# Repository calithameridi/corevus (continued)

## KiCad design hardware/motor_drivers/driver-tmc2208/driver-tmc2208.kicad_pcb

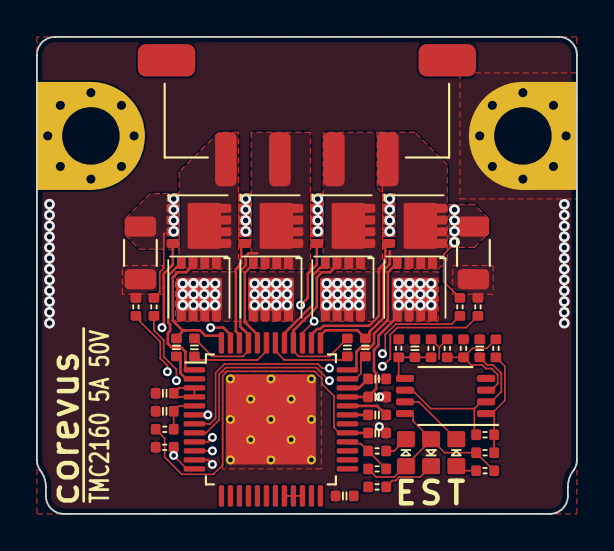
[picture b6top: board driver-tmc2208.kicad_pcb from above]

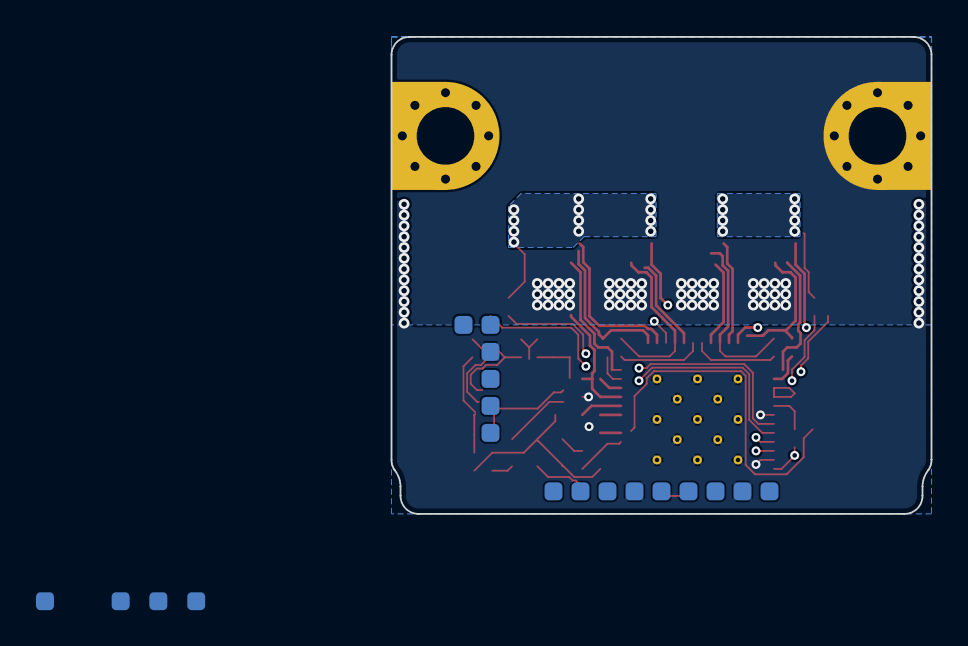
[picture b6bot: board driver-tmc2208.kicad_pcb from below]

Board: 4 copper layers, 30.0 x 26.5 mm, 67 parts (19 on the bottom side), 49 nets.

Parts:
C1: 100nF 16V; 0402C
C2: 22nF 100V; 0402C
C3, C5: 1µF; 0402C
C4, C6, C8, C9, C10, C11: 1μF; 0402C
C7: 100nF 100V; 0402C
C12: 4.7nF; 0402C
C13: 10nF; 0402C
D1: G; 0603LED
D2: Y; 0603LED
D3: R; 0603LED
H1: VM; MountingHole_M3_Driver
H2: Gnd; MountingHole_M3_Driver
M1: Micro-Fit 3.0; XKB_X3025WRS-04D
Q1, Q2, Q3, Q4, Q5, Q6, Q7, Q8: 30N06; MOSFET_DFN8
R1, R16: 1kΩ; 0402R
R2, R3: 10kΩ; 0402R
R4: 2.2Ω; 0402R
R5: AkΩ; 0402R
R6: BkΩ; 0402R
R7: CkΩ; 0402R
R8, R9, R11, R12: 47Ω; 0402R
R10, R13: 30mΩ; R_1206_3216Metric
R14: DkΩ; 0402R
R15: EkΩ; 0402R
R17: 200Ω; 0402R
R20: 4.7kΩ; 0402R
T1, T5, T12: GND; LGA_Land
T2: CLK; LGA_Land
T3: 12V; LGA_Land
T4: SCK; LGA_Land
T6: SDI; LGA_Land
T7: SDO; LGA_Land
T8: VCC; LGA_Land
T9: Therm; LGA_Land
T10: CS0; LGA_Land
T11: STEP; LGA_Land
T13: DIR; LGA_Land
T14: EN; LGA_Land
T17: DIAG0; LGA_Land
T18: DIAG1; LGA_Land
T19: ENCA; LGA_Land
T20: ENCB; LGA_Land
T21: ENCN; LGA_Land
TH1: 10kΩ 3950K; 0402R
U1: TMC2160; TMCx160
U2: LM393; MSOP-8_3x3mm_P0.65mm

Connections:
+12V: C6.1, T3.1, U1.3 (12VOUT), U1.4 (VSA)
+48V: C1.2, C7.1, H1.1, Q1.5 (D), Q1.6 (D), Q1.7 (D), Q1.8 (D), Q3.5 (D), Q3.6 (D), Q3.7 (D), Q3.8 (D), Q5.5 (D), Q5.6 (D), Q5.7 (D), Q5.8 (D), Q7.5 (D), Q7.6 (D), Q7.7 (D), Q7.8 (D), U1.33 (VS)
/A1: C10.2, M1.3, Q5.1 (S), Q5.2 (S), Q5.3 (S), Q6.5 (D), Q6.6 (D), Q6.7 (D), Q6.8 (D), U1.40 (BMA1)
/A2: C11.2, M1.4, Q7.1 (S), Q7.2 (S), Q7.3 (S), Q8.5 (D), Q8.6 (D), Q8.7 (D), Q8.8 (D), U1.37 (BMA2)
/B1: C8.2, M1.1, Q1.1 (S), Q1.2 (S), Q1.3 (S), Q2.5 (D), Q2.6 (D), Q2.7 (D), Q2.8 (D), U1.48 (BMB1)
/B2: C9.2, M1.2 (-), Q3.1 (S), Q3.2 (S), Q3.3 (S), Q4.5 (D), Q4.6 (D), Q4.7 (D), Q4.8 (D), U1.45 (BMB2)
/Clk: R3.1, T2.1, U1.12 (CLK)
/Diag0: T17.1, U1.26 (DIAG0)
/Diag1: R16.2, T18.1, U1.27 (DIAG1)
/Dir: T13.1, U1.18 (DIR)
/HA1: Q5.4 (G), U1.41 (HA1)
/HA2: Q7.4 (G), U1.36 (HA2)
/HB1: Q1.4 (G), U1.1 (HB1)
/HB2: Q3.4 (G), U1.44 (HB2)
/LA1: Q6.4 (G), U1.39 (LA1)
/LA2: Q8.4 (G), U1.38 (LA2)
/LB1: Q2.4 (G), U1.47 (LB1)
/LB2: Q4.4 (G), U1.46 (LB2)
/SCK: T4.1, U1.14 (SCK/CFG2)
/SDI: T6.1, U1.15 (SDI/CFG1)
/SDO: T7.1, U1.16 (SDO/CFG0)
/SRAH: R11.2, U1.8 (SRAH)
/SRAL: R12.2, U1.7 (SRAL)
/SRBH: R8.2, U1.9 (SRBH)
/SRBL: R9.2, U1.10 (SRBL)
/Step: T11.1, U1.17 (STEP)
/THERM: C13.1, R20.1, T9.1, TH1.1, U2.5 (+)
/~CS: T10.1, U1.13 (~CS/CFG3)
/~En: R1.2, R2.2, T14.1, U1.28 (~DRV_EN)
GND: C3.1, C4.1, C5.1, C6.2, C7.2, C12.2, C13.2, H2.1, R3.2, R6.2, R9.1, R10.2, R12.1, R13.2, T1.1, T5.1, T12.1, TH1.2, U1.6 (GNDA), U1.11 (TST_MODE), U1.19 (GNDD), U1.30 (GNDD), U1.49 (EP), U2.4 (V-)
unnamed: D1.1 (K), R1.1
unnamed: D2.1 (K), R16.1
unnamed: D3.2 (A), R17.2
unnamed: D3.1 (K), U2.7
unnamed: Q2.1 (S), Q2.2 (S), Q2.3 (S), Q4.1 (S), Q4.2 (S), Q4.3 (S), R8.1, R10.1
unnamed: Q6.1 (S), Q6.2 (S), Q6.3 (S), Q8.1 (S), Q8.2 (S), Q8.3 (S), R11.1, R13.1
unnamed: R7.2, R14.2, R15.1, U2.1
unnamed: C4.2, R4.1, U1.5 (5VOUT)
unnamed: C10.1, U1.42 (CA1)
unnamed: C11.1, U1.35 (CA2)
unnamed: C8.1, U1.2 (CB1)
unnamed: C9.1, U1.43 (CB2)
unnamed: C2.2, U1.32 (CPI)
unnamed: C2.1, U1.31 (CPO)
unnamed: C5.2, R4.2, U1.29 (VCC)
unnamed: C1.1, U1.34 (VCP)
unnamed: R5.1, R6.1, R7.1, U2.3 (+)
unnamed: C12.1, R15.2, U2.2 (-), U2.6 (-)
VCC: C3.2, D1.2 (A), D2.2 (A), R2.1, R5.2, R14.1, R17.1, R20.2, T8.1, U1.20 (VCC_IO), U1.21 (VCC_IO), U1.22 (SPI_MODE), U2.8 (V+)

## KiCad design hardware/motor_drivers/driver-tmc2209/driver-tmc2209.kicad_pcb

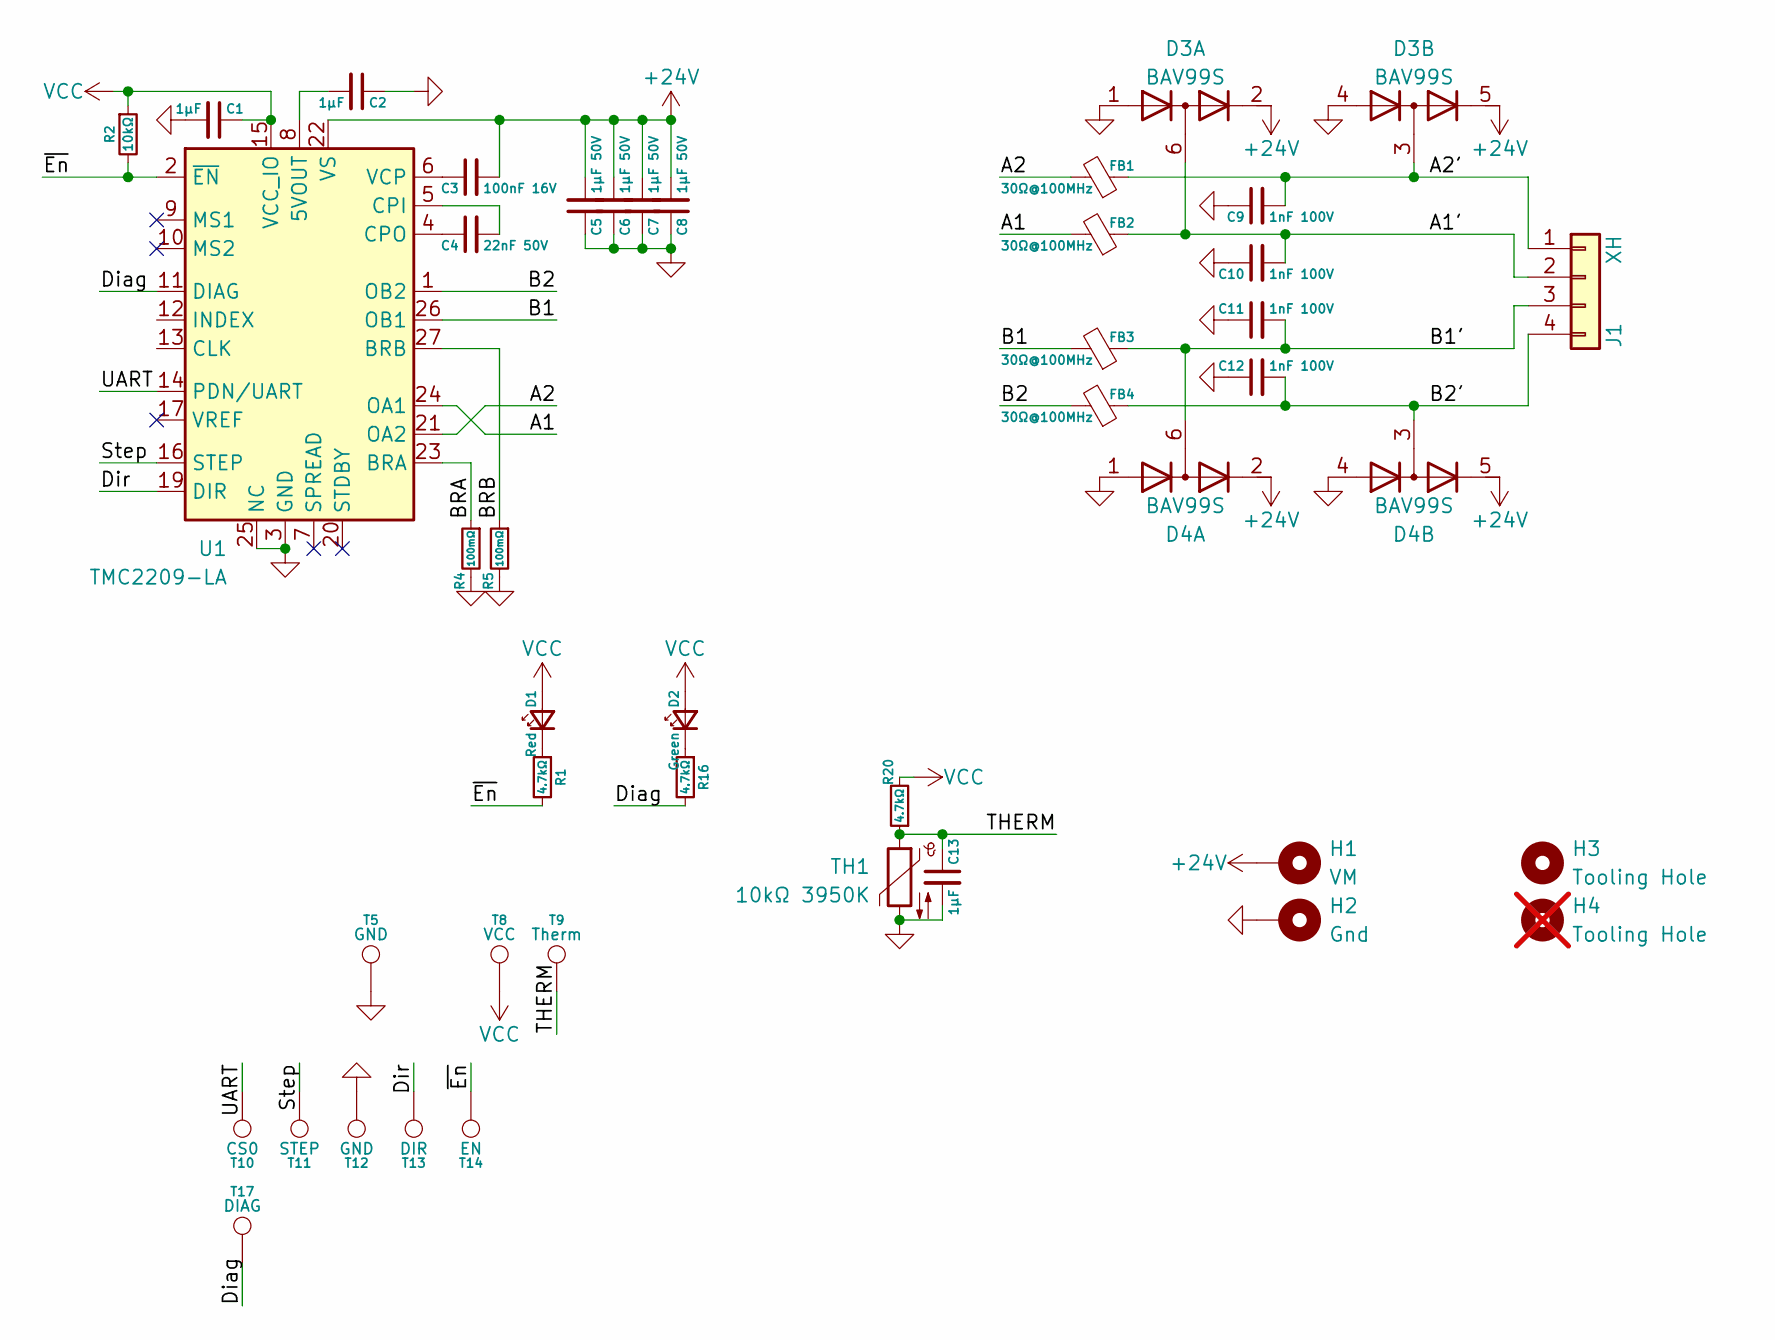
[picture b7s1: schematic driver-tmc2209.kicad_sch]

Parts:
C1, C2: 1μF; 0402C; LCSC C1525
C3: 100nF 16V; 0402C; LCSC C1525
C4: 22nF 50V; 0402C; LCSC C1532
C5, C6, C7, C8: 1μF 50V; 0603C; LCSC C15849
C9, C10, C11, C12: 1nF 100V; 0402C
C13: 1μF; 0402C
D1: Red; 0402LED
D2: Green; 0402LED
D3, D4: BAV99S; SOT-363_SC-70-6
FB1, FB2, FB3, FB4: 30Ω@100MHz; R_0805_2012Metric
H1: VM; MountingHole_M3_Driver_Corner
H2: Gnd; MountingHole_M3_Driver_Corner
H3: Tooling Hole; ToolingHole
H4: Tooling Hole; ToolingHole; not fitted
J1: XH; XH_1x04_SMD_Vertical
R1, R16, R20: 4.7kΩ; 0402R
R2: 10kΩ; 0402R
R4, R5: 100mΩ; R_0805_2012Metric; LCSC C382279
T5, T12: GND; LGA_Land_2.5mm
T8: VCC; LGA_Land_2.5mm
T9: Therm; LGA_Land_2.5mm
T10: CS0; LGA_Land_2.5mm
T11: STEP; LGA_Land_2.5mm
T13: DIR; LGA_Land_2.5mm
T14: EN; LGA_Land_2.5mm
T17: DIAG; LGA_Land_2.5mm
TH1: 10kΩ 3950K; 0402R
U1: TMC2209-LA; TMC220x

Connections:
+24V: C3.2, C5.2, C6.2, C7.2, C8.2, D3.2 (K2), D3.5 (K4), D4.2 (K2), D4.5 (K4), H1.1, U1.22 (VS), U1.28 (VS)
/A1: FB2.2, U1.24 (OA1)
/A1': C10.2, D3.6 (K3A4), FB2.1, J1.2
/A2: FB1.2, U1.21 (OA2)
/A2': C9.2, D3.3 (K1A2), FB1.1, J1.1
/B1: FB3.2, U1.26 (OB1)
/B1': C11.2, D4.6 (K3A4), FB3.1, J1.3
/B2: FB4.2, U1.1 (OB2)
/B2': C12.2, D4.3 (K1A2), FB4.1, J1.4
/BRA: R4.1, U1.23 (BRA)
/BRB: R5.1, U1.27 (BRB)
/Diag: R16.2, T17.1, U1.11 (DIAG)
/Dir: T13.1, U1.19 (DIR)
/Step: T11.1, U1.16 (STEP)
/THERM: C13.1, R20.1, T9.1, TH1.1
/UART: T10.1, U1.14 (PDN/UART)
/~En: R1.2, R2.2, T14.1, U1.2 (~EN)
GND: C1.2, C2.1, C5.1, C6.1, C7.1, C8.1, C9.1, C10.1, C11.1, C12.1, C13.2, D3.1 (A1), D3.4 (A3), D4.1 (A1), D4.4 (A3), H2.1, R4.2, R5.2, T5.1, T12.1, TH1.2, U1.3 (GND), U1.18 (Gnd), U1.25 (NC), U1.29 (Pad)
unnamed: D1.1 (K), R1.1
unnamed: D2.1 (K), R16.1
unnamed: C2.2, U1.8 (5VOUT)
unnamed: C4.2, U1.5 (CPI)
unnamed: C4.1, U1.4 (CPO)
unnamed: C3.1, U1.6 (VCP)
VCC: C1.1, D1.2 (A), D2.2 (A), R2.1, R20.2, T8.1, U1.15 (VCC_IO)

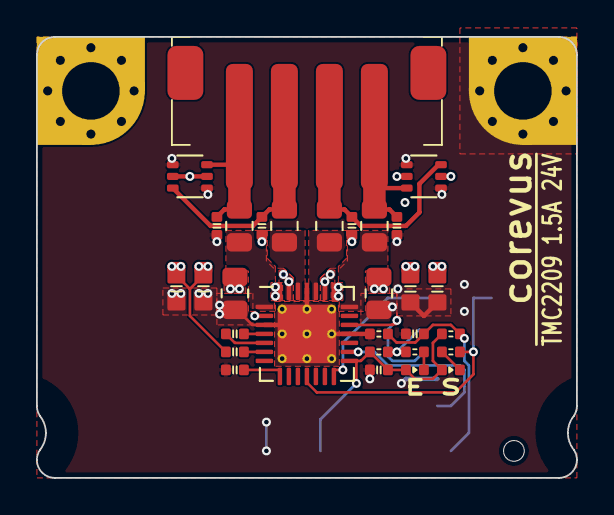
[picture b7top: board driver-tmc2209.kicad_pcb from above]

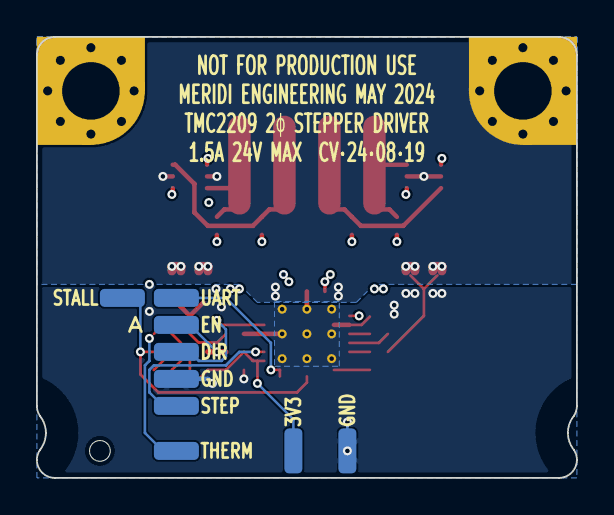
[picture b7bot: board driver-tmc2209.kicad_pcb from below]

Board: 4 copper layers, 30.0 x 24.5 mm, 42 parts (9 on the bottom side), 25 nets.

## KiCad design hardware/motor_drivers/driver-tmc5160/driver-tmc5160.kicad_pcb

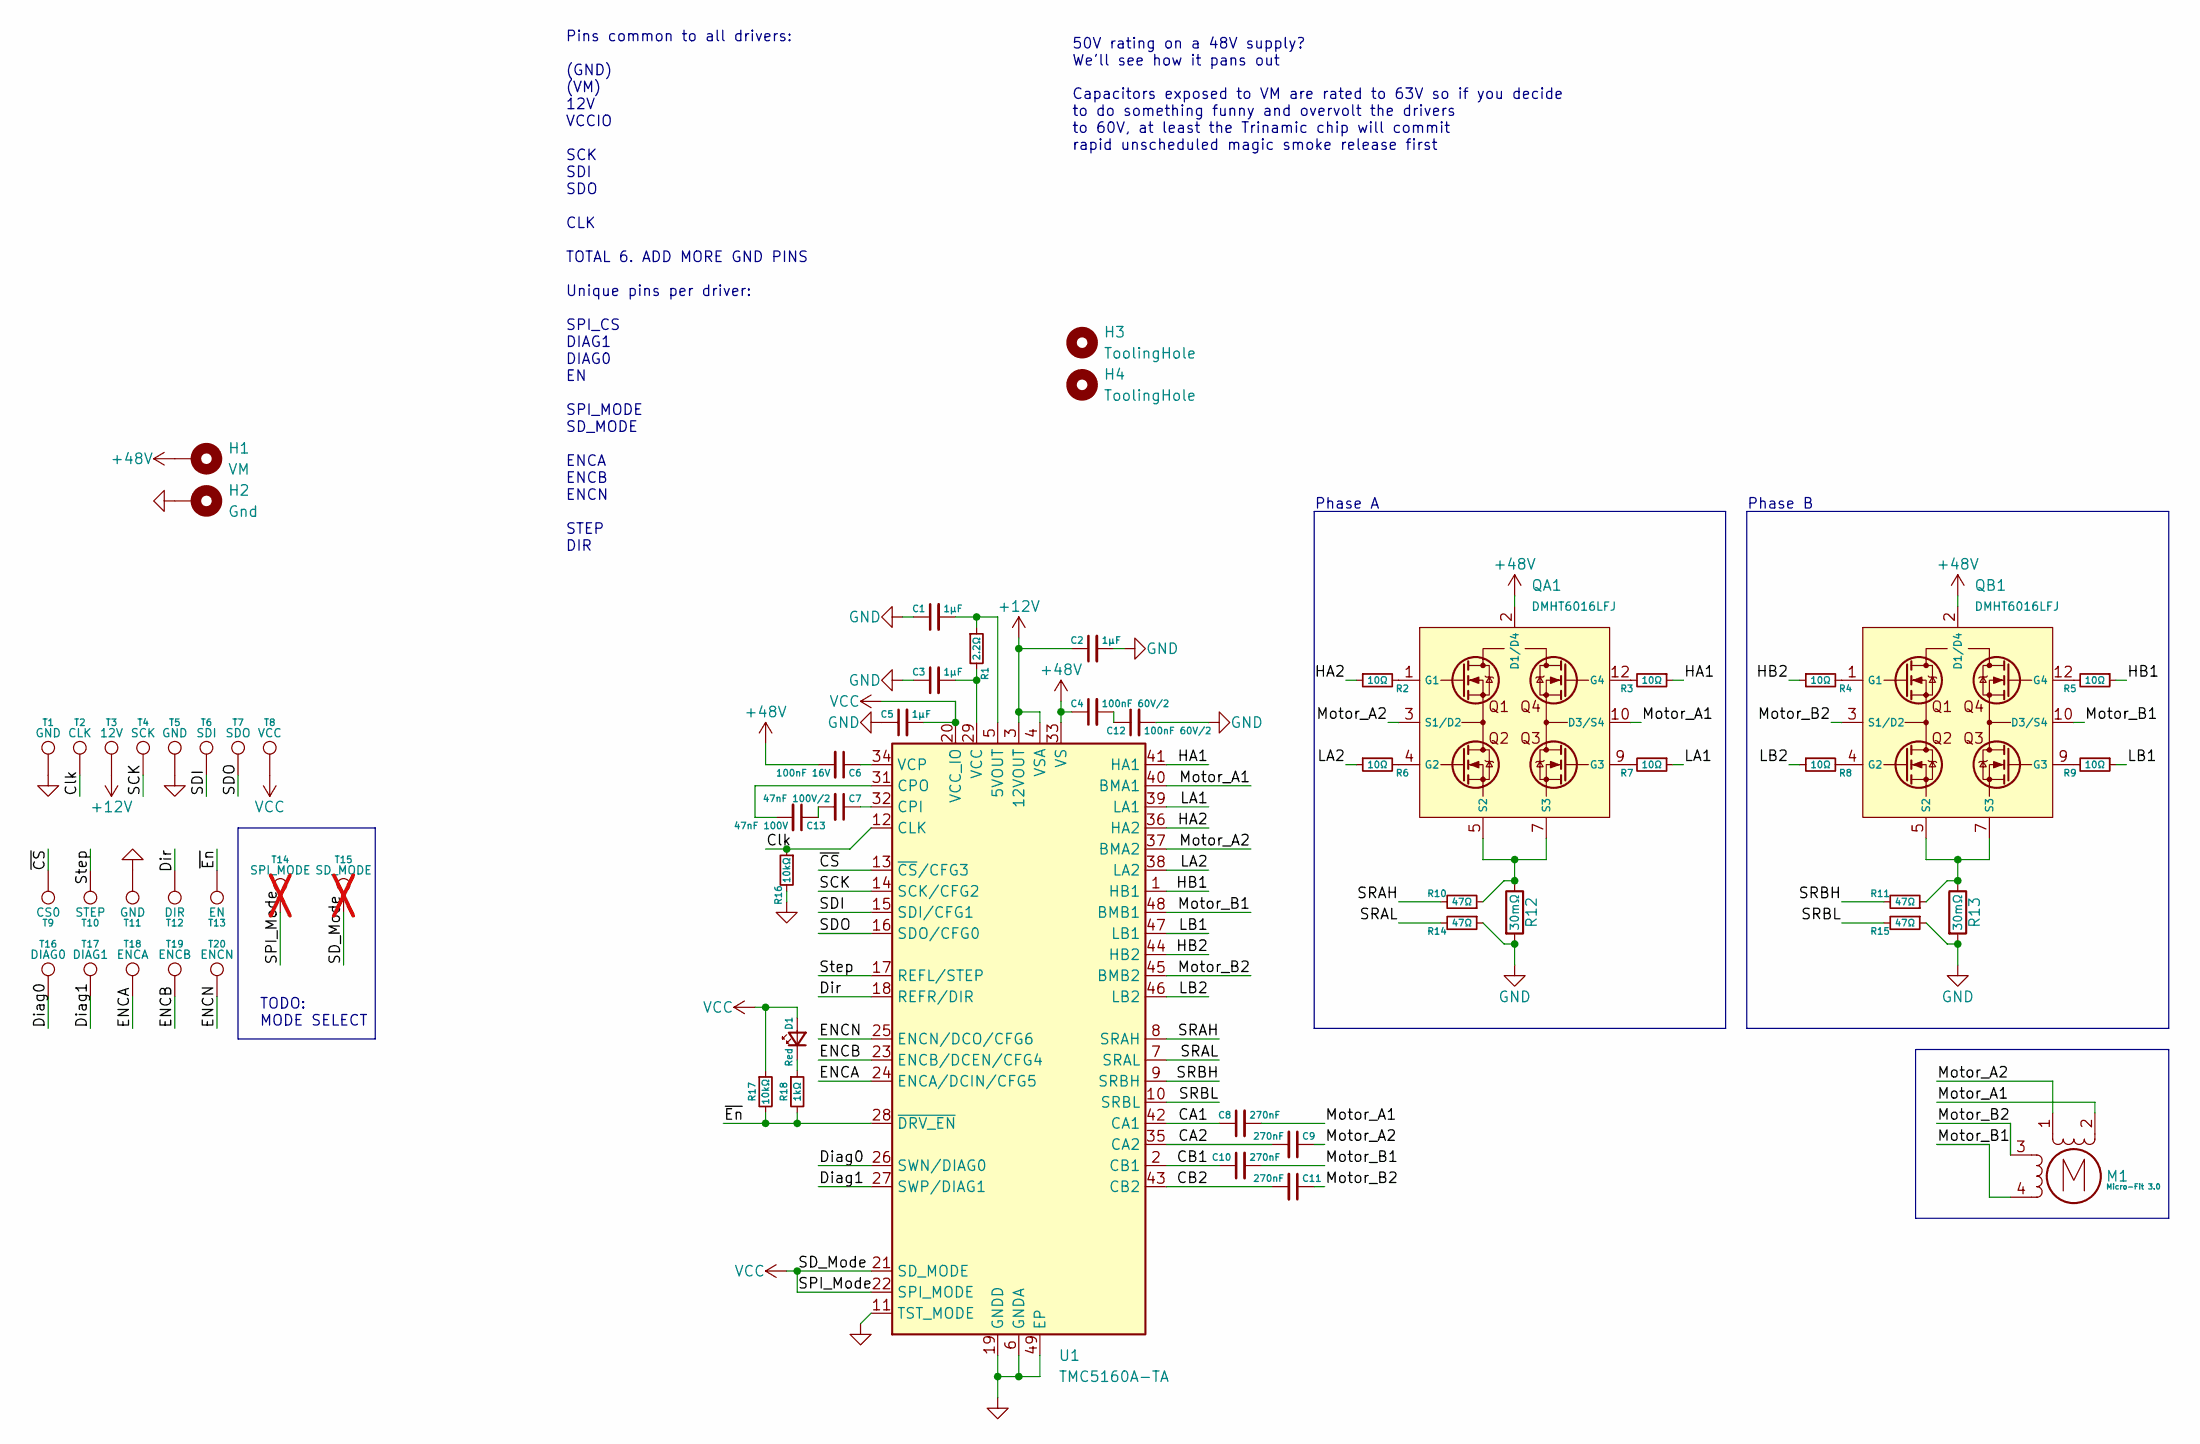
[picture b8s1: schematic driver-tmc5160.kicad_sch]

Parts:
C1, C2: 1μF; 0402C
C3, C5: 1µF; 0402C
C4, C12: 100nF 60V/2; 0402C
C6: 100nF 16V; 0402C
C7: 47nF 100V/2; 0402C
C8, C9, C10, C11: 270nF; 0402C
C13: 47nF 100V; 0402C
D1: Red; 0603LED
H1: VM; MountingHole_M3_Driver
H2: Gnd; MountingHole_M3_Driver
H3, H4: ToolingHole
M1: Micro-Fit 3.0; XKB_X8821WRS-04
QA1: DMHT6016LFJ; V-DFN5045-12-Type-B; LCSC C460986
QB1: DMHT6016LFJ; V-DFN5045-12-Type-B; LCSC C460986
R1: 2.2Ω; 0402R
R2, R3, R4, R5, R6, R7, R8, R9: 10Ω; 0402R
R10, R11, R14, R15: 47Ω; 0402R
R12, R13: 30mΩ; R_1206_3216Metric
R16, R17: 10kΩ; 0402R
R18: 1kΩ; 0402R
T1, T5, T11: GND; LGA_Land
T2: CLK; LGA_Land
T3: 12V; LGA_Land
T4: SCK; LGA_Land
T6: SDI; LGA_Land
T7: SDO; LGA_Land
T8: VCC; LGA_Land
T9: CS0; LGA_Land
T10: STEP; LGA_Land
T12: DIR; LGA_Land
T13: EN; LGA_Land
T14: SPI_MODE; LGA_Land; not fitted
T15: SD_MODE; LGA_Land; not fitted
T16: DIAG0; LGA_Land
T17: DIAG1; LGA_Land
T18: ENCA; LGA_Land
T19: ENCB; LGA_Land
T20: ENCN; LGA_Land
U1: TMC5160A-TA; TQFP-48-1EP_7x7mm_P0.5mm_EP5x5mm_ThermalVias

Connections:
+12V: C2.1, T3.1, U1.3 (12VOUT), U1.4 (VSA)
+48V: C4.1, C6.2, H1.1, QA1.2 (D1/D4), QA1.11 (D1/D4), QA1.P1 (D1/D4), QB1.2 (D1/D4), QB1.11 (D1/D4), QB1.P1 (D1/D4), U1.33 (VS)
/CA1: C8.1, U1.42 (CA1)
/CA2: C9.2, U1.35 (CA2)
/CB1: C10.1, U1.2 (CB1)
/CB2: C11.2, U1.43 (CB2)
/Clk: R16.1, T2.1, U1.12 (CLK)
/Diag0: T16.1, U1.26 (SWN/DIAG0)
/Diag1: T17.1, U1.27 (SWP/DIAG1)
/Dir: T12.1, U1.18 (REFR/DIR)
/ENCA: T18.1, U1.24 (ENCA/DCIN/CFG5)
/ENCB: T19.1, U1.23 (ENCB/DCEN/CFG4)
/ENCN: T20.1, U1.25 (ENCN/DCO/CFG6)
/HA1: R3.1, U1.41 (HA1)
/HA2: R2.1, U1.36 (HA2)
/HB1: R5.1, U1.1 (HB1)
/HB2: R4.1, U1.44 (HB2)
/LA1: R7.1, U1.39 (LA1)
/LA2: R6.1, U1.38 (LA2)
/LB1: R9.1, U1.47 (LB1)
/LB2: R8.1, U1.46 (LB2)
/Motor_A1: C8.2, M1.2 (-), QA1.10 (D3/S4), QA1.P3 (D3/S4), U1.40 (BMA1)
/Motor_A2: C9.1, M1.1, QA1.3 (S1/D2), QA1.P2 (S1/D2), U1.37 (BMA2)
/Motor_B1: C10.2, M1.4, QB1.10 (D3/S4), QB1.P3 (D3/S4), U1.48 (BMB1)
/Motor_B2: C11.1, M1.3, QB1.3 (S1/D2), QB1.P2 (S1/D2), U1.45 (BMB2)
/SCK: T4.1, U1.14 (SCK/CFG2)
/SDI: T6.1, U1.15 (SDI/CFG1)
/SDO: T7.1, U1.16 (SDO/CFG0)
/SRAH: R10.2, U1.8 (SRAH)
/SRAL: R14.2, U1.7 (SRAL)
/SRBH: R11.2, U1.9 (SRBH)
/SRBL: R15.2, U1.10 (SRBL)
/Step: T10.1, U1.17 (REFL/STEP)
/~CS: T9.1, U1.13 (~CS/CFG3)
/~En: R17.2, R18.2, T13.1, U1.28 (~DRV_EN)
GND: C1.1, C2.2, C3.1, C5.1, C12.2, H2.1, R12.2, R13.2, R14.1, R15.1, R16.2, T1.1, T5.1, T11.1, U1.6 (GNDA), U1.11 (TST_MODE), U1.19 (GNDD), U1.30 (GNDD), U1.49 (EP)
unnamed: C4.2, C12.1
unnamed: C7.2, C13.1
unnamed: D1.1 (K), R18.1
unnamed: QA1.1 (G1), R2.2
unnamed: QA1.4 (G2), R6.2
unnamed: QA1.9 (G3), R7.2
unnamed: QA1.12 (G4), R3.2
unnamed: QA1.5 (S2), QA1.6 (S2), QA1.7 (S3), QA1.8 (S3), R10.1, R12.1
unnamed: QB1.1 (G1), R4.2
unnamed: QB1.4 (G2), R8.2
unnamed: QB1.9 (G3), R9.2
unnamed: QB1.12 (G4), R5.2
unnamed: QB1.5 (S2), QB1.6 (S2), QB1.7 (S3), QB1.8 (S3), R11.1, R13.1
unnamed: C1.2, R1.1, U1.5 (5VOUT)
unnamed: C7.1, U1.32 (CPI)
unnamed: C13.2, U1.31 (CPO)
unnamed: C3.2, R1.2, U1.29 (VCC)
unnamed: C6.1, U1.34 (VCP)
VCC: C5.2, D1.2 (A), R17.1, T8.1, T14.1, T15.1, U1.20 (VCC_IO), U1.21 (SD_MODE), U1.22 (SPI_MODE)

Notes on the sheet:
50V rating on a 48V supply? We'll see how it pans out
Phase A
Phase B
Capacitors exposed to VM are rated to 63V so if you decide to do something funny and overvolt the drivers to 60V, at least the Trinamic chip will commit rapid unscheduled magic smoke release first
TODO: MODE SELECT
Pins common to all drivers: (GND) (VM) 12V VCCIO SCK SDI SDO CLK TOTAL 6. ADD MORE GND PINS Unique pins per driver: SPI_CS DIAG1 DIAG0 EN SPI_MODE SD_MODE ENCA ENCB ENCN STEP DIR

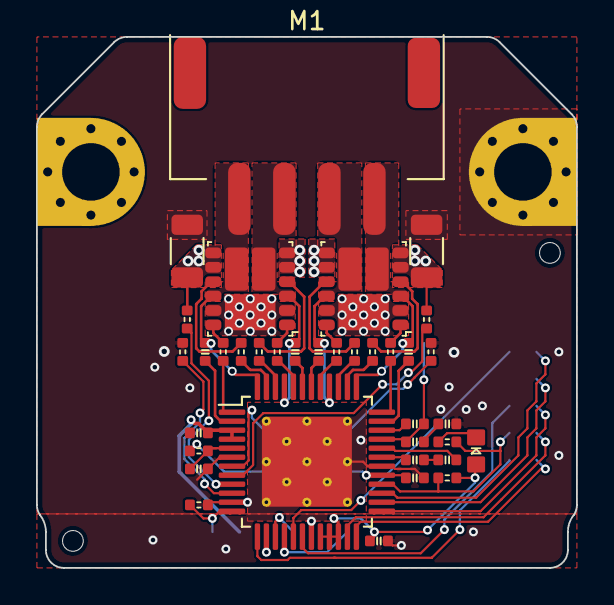
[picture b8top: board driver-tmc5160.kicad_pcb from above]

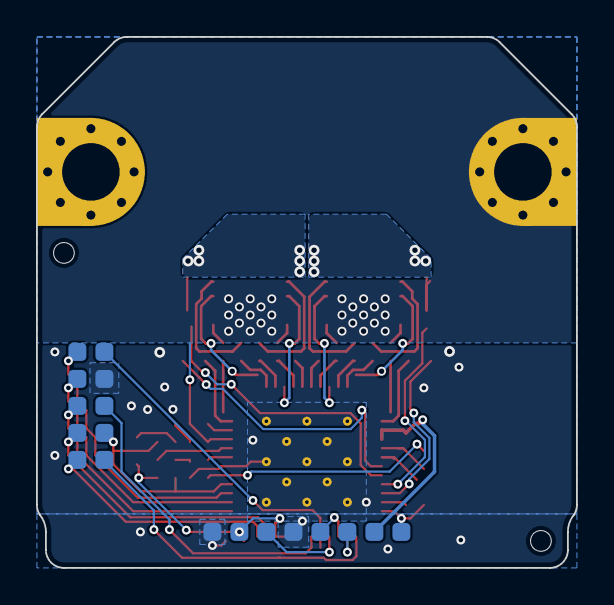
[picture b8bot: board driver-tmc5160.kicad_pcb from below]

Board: 2 copper layers, 30.0 x 29.5 mm, 58 parts (18 on the bottom side), 55 nets.

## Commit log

2023-06-15 initialized project
2023-06-18 test reworking of directory structure
2023-06-18 lmao
2023-06-23 added preliminary LGA layout for motor expansion module
2023-07-22 further work on motor drivers and connector layout, additional symbols/footprints/models
2023-07-28 added fan / heater ports to mainboard, and footprints for switches, transistors, etc.
2023-08-09 saving mainboard, gonna tear out the entire thing and redo in 4-layer
2023-08-19 further board edits, mostly done with power planes, heaters, fans, motor channels, starting work on microcontroller signals
2023-08-24 redid mainboard, added probe wiring, replacing ncp chip with LM5160 for now
2023-08-30 nearing first prototype woot! copyediting over entire board, fixed some mistakes
2023-08-31 test new gitignore with completed mainboard
2023-09-01 test gitignore edit
2023-09-05 redoing board for version alpha 0.2
2023-09-09 added components and further work on PCB layout design
2023-09-21 tested SMD style XH connectors — didn't work very well alas
2023-09-26 fan ports
2023-09-29 this is immediately before i switch the terminus USB hub with the corechips
2023-09-29 v0.2 feature complete
2023-10-01 added more 3D models and created first few renders
2023-10-08 adopt corevus-g designation for current mainboard, cleanup
2023-10-10 finish corevus-g, create file for corevus-k
2023-10-14 test
2023-10-17 add corevus-g alpha markdown description
2023-10-17 Update and rename Corevus-G Alpha program(4)(1)(1).md to corevus-g-alpha-users-guide
2023-10-17 add'l work on tmc2160 driver, i think i'm finally converging on a layout i'm satisfied with
2023-10-20 aonteuhasntoidanouidoenuthidntoehuid
2023-10-20 corevus-g board mounts
    Added board mounts for the corevus-g, supports extrusion mount using M3, M4 or M5 or din rail mount, both usable in vertical or horizontal configuration
2023-10-20 config file
    Updated the board configurator
2023-10-20 config fix
    Fixed issue with config file
2023-11-26 just discovered that corevus-g v0.3 cooks itself wonderful
2023-12-12 weird fucking shit where CvG-v0.3 schematics went poof
2023-12-16 version control appears to have magically disappeared the single and dual 2160 driver files :(((((((((, but got some work done on CvG nonetheless
2024-01-08 v0.4 mostly complete, board needs minor revisions (e.g. pin swap)
2024-01-08 added v0.4 image
2024-01-28 CvG v0.4 complete, now updating documentation
2024-01-28 cleanup
2024-01-28 more cleanup wee
2024-01-28 config docs
2024-01-28 fix readme link
2024-01-28 fix link
2024-02-01 add more documentation
2024-02-01 update link
2024-02-01 aoesunhtaoesnuhnst
2024-02-01 link testing
2024-02-01 aoeuntshaoesun
2024-02-03 real shit?
2024-02-03 snhnthsnhnsthsnthnsthnsthntsh
2024-02-03 snhsn
2024-02-03 atoehusntaoehntu
2024-02-05 updated config setup
2024-02-05 aoeuaoeuaoeu
2024-02-06 added section to cfg setup on bugfix
2024-02-07 SUPER CURSED BUG
2024-02-10 updated with h723 fix workaround info
2024-02-10 add link
2024-02-12 polished footprints
2024-02-12 added info on make -j4 to config setup manual
2024-02-15 non-working commit, moved around various connectors etc in preparation for v0.5
2024-03-24 this should be hardware revs of CvG v0.5 (broken), CvM++ v0.1 (broken, also not final name), and the tmc2209 driver
2024-04-05 corevus toolboard v0.2 release (working), corevus-g v0.2 release (very much not working), m++ v0.1 (not working, needs a lot of bodges)
2024-04-15 made some edit to footprints. also my previous commit should have specified cvg v0.5 borked, not v0.2
2024-04-16 v0.3 toolboard nearing completion (just need to make the production files), also made panelization test board
2024-04-17 finished production data for toolboard v0.3, just waiting on parts eeeeeeee
2024-05-07 why not
2024-05-26 should be up to date for cvg v0.6 and latest protected drivers
2024-05-26 lmao you didn't see that
2024-05-28 Added v0.6 manual (work in progress)
2024-05-28 Added image to wip v0.6 manual
2024-05-29 v0.6 add
2024-06-18 Added details on fan / motor voltage selection
2024-07-09 added ctb v0.3 and dual 2160, fixed typo in v0.6 manual
2024-07-24 last before i go on v0.7
2024-08-08 cleaned up corevus toolboard schematics to be more presentable
2024-08-13 48v extruder driver first prototype, dual tmc2160 polish for next rev
2024-08-15 last commit before i delete 2 layers from the dual tmc2160
2024-09-03 Added STEP and Parasolid mechanical files for Corevus-G v0.6, added TMC2160 + Heater module, added toolboard 4x thermistor expansion, added toolboard MAX31856 thermocouple ADC expansion
2024-09-03 minor file rename
2024-09-11 added corevus driver module images and documentation
2025-02-08 update toolboard, change documentation
2025-02-24 add toolboard documentation
